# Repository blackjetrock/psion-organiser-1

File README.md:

# psion-organiser-1
Psion Organiser 1

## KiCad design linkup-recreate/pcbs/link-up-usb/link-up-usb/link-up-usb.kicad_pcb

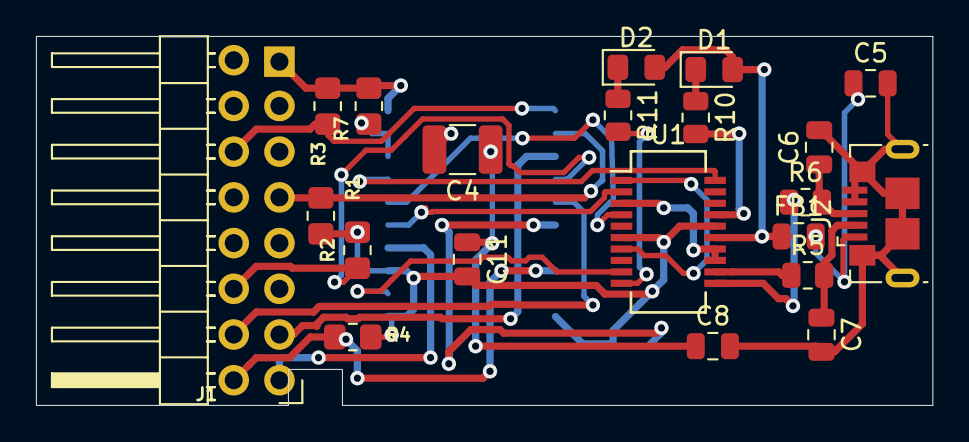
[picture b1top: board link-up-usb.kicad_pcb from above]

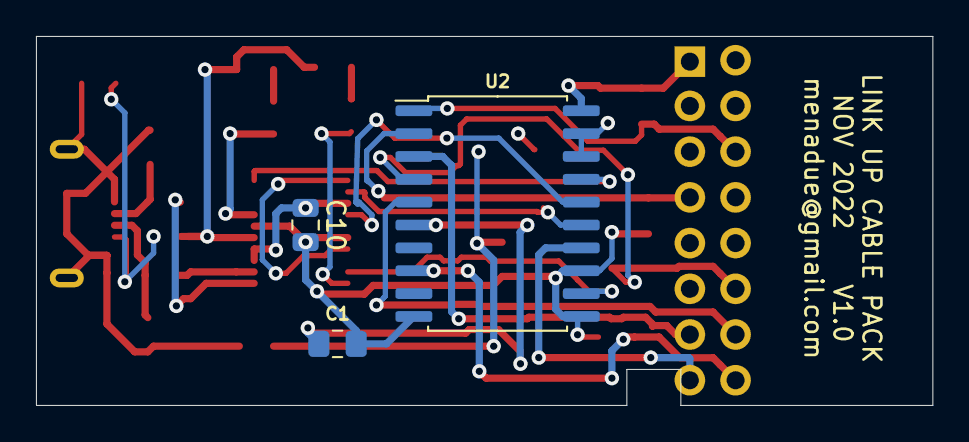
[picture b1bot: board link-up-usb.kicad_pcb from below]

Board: 4 copper layers, 49.8 x 20.5 mm, 24 parts (3 on the bottom side), 27 nets.

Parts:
C1: 100nF?; C_0805_2012Metric_Pad1.18x1.45mm_HandSolder
C4: 4u7; C_1210_3225Metric_Pad1.33x2.70mm_HandSolder
C5: 10nF; C_0805_2012Metric
C6, C7: 47pF; C_0805_2012Metric
C8, C10, C11: 100nF; C_0805_2012Metric
D1, D2: SMD LED; LED_0805_2012Metric_Pad1.15x1.40mm_HandSolder
FB1: Laird Technologies Part # MI0805K400R-10; C_0805_2012Metric
J1: Conn_02x08_Odd_Even; Psion_datapak_2x08_P2.54mm_Horizontal
J2: Connector_USB_B_Micro; USB_Micro-B_GCT_USB3076-30-A
R1, R2, R3, R4, R7: 47k; R_0805_2012Metric_Pad1.20x1.40mm_HandSolder
R5, R6: 27R; R_0805_2012Metric
R10, R11: 470R; R_0805_2012Metric
U1: FT231XS; SSOP-20_3.9x8.7mm_P0.635mm
U2: 40244; SOIC-20W_7.5x12.8mm_P1.27mm

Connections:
+5V: D1.2, D2.2, FB1.1, U1.15
+5V_LOGIC: C4.1, C8.1, C11.1
CTS: U1.9, U2.12
DTR_DSR: U1.1, U1.7
GND: C1.2, C4.2, C5.2, C6.2, C7.2, C8.2, C10.2, C11.2, J1.3, J2.4, J2.5, J2.6, R1.2, R2.2, R4.2, U1.6, U1.16, U2.10, U2.11, U2.13
unnamed: C5.1, FB1.2, J2.1
unnamed: C6.1, J2.3, R6.2
unnamed: C7.1, J2.2, R5.2
unnamed: C10.1, U1.3, U1.13, U1.14
unnamed: D1.1, R10.1
unnamed: D2.1, R11.1
unnamed: R5.1, U1.12
unnamed: R6.1, U1.11
unnamed: R7.2, U2.18, U2.19
unnamed: R10.2, U1.17
unnamed: R11.2, U1.10
RTS: U1.2, U2.15
RXD: U1.4, U2.16
SD0: J1.16, R4.1, U2.8
SD1: J1.15, U2.14
SD2: J1.14, U2.5
SD3: J1.13, U2.3
SD4: J1.12, R2.1, U2.4
SMR: J1.7, R1.1, U2.2
SS: J1.6, R3.2, U2.1
SVCC: C1.1, J1.1, R3.1, R7.1, U2.6, U2.20
TXD: U1.20, U2.17

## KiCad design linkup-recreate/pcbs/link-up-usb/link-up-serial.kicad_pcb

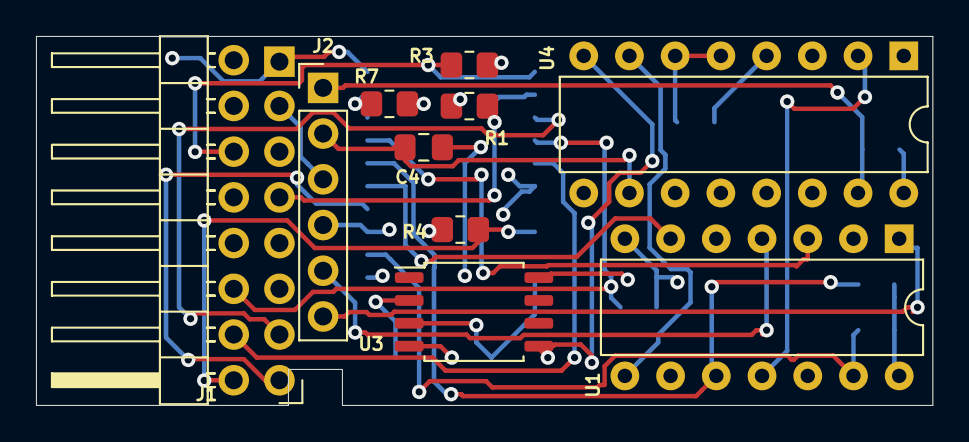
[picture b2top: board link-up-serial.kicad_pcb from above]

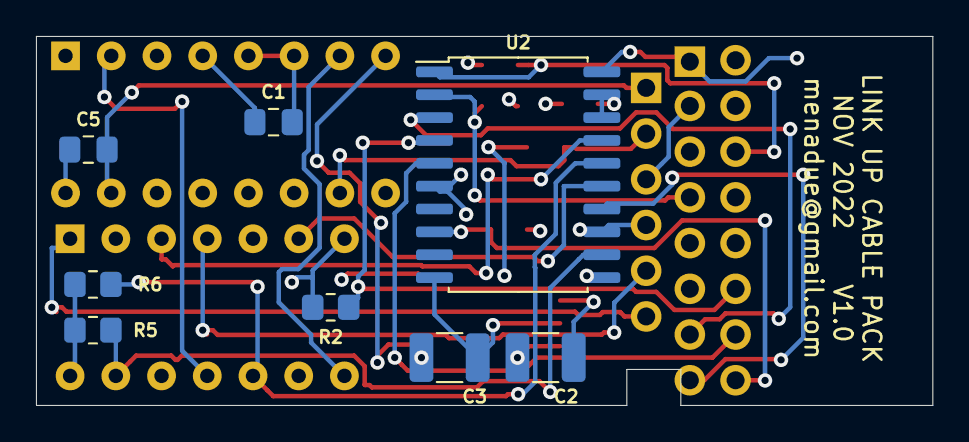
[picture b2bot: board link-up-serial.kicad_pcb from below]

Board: 4 copper layers, 49.8 x 20.5 mm, 18 parts (8 on the bottom side), 25 nets.

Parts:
C1: 100nF?; C_0805_2012Metric_Pad1.18x1.45mm_HandSolder
C2, C3: 10uF 16V; C_1210_3225Metric_Pad1.33x2.70mm_HandSolder
C4, C5: 20pF - 10nF; C_0805_2012Metric_Pad1.18x1.45mm_HandSolder
J1: Conn_02x08_Odd_Even; Psion_datapak_2x08_P2.54mm_Horizontal
J2: Conn_01x06_Female; PinHeader_1x06_P2.54mm_Vertical
R1, R2, R3, R4, R7: 47k; R_0805_2012Metric_Pad1.20x1.40mm_HandSolder
R5, R6: 10k; R_0805_2012Metric_Pad1.20x1.40mm_HandSolder
U1: 1489; DIP-14_W7.62mm
U2: 40244; SOIC-20W_7.5x12.8mm_P1.27mm
U3: ICL7660; SOP-8_5.28x5.23mm_P1.27mm
U4: DS3691; DIP-16_W7.62mm

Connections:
-5V: C3.1, U3.5, U4.8
BLUE: J2.6, U1.1
BROWN: C5.2, J2.1, U4.15
CTS_X: U1.11, U4.2
CTS_Y: R5.2, U1.13, U2.12
GREEN: J2.5, U1.4
unnamed: C2.1, U3.2
unnamed: C2.2, U3.4
unnamed: C4.2, U4.9
unnamed: C5.1, U4.16
unnamed: R7.2, U2.18, U2.19
ORANGE: C1.2, C3.2, J1.3, J2.3, J2.4, R1.2, R2.2, R4.2, U1.7, U2.10, U2.11, U2.13, U3.3, U4.3, U4.5, U4.6
RED: C4.1, J2.2, U4.10
RTS_X: U1.6, U2.15
RXD_X: U1.8, U4.7
RXD_Y: R6.2, U1.10, U2.16
SD0: J1.16, R4.1, U2.8
SD1: J1.15, U2.14
SD2: J1.14, U2.5
SD3: J1.13, U2.3
SD4: J1.12, R2.1, U2.4
SMR: J1.7, R1.1, U2.2
SS: J1.6, R3.2, U2.1
SVCC: C1.1, J1.1, R3.1, R5.1, R6.1, R7.1, U1.14, U2.6, U2.20, U3.8, U4.1, U4.4
TXD_X: U1.3, U2.17

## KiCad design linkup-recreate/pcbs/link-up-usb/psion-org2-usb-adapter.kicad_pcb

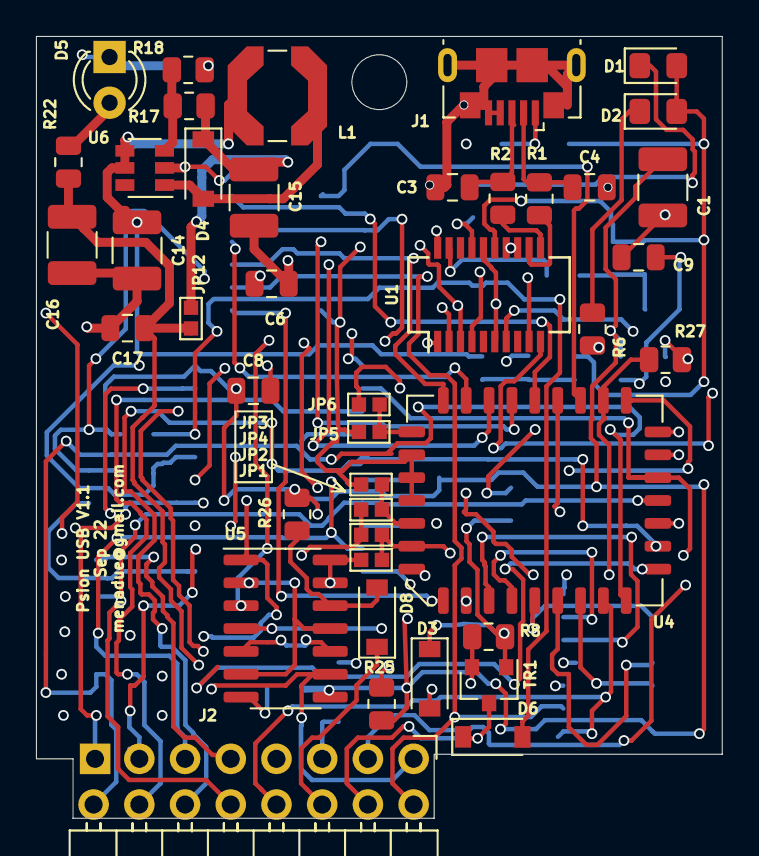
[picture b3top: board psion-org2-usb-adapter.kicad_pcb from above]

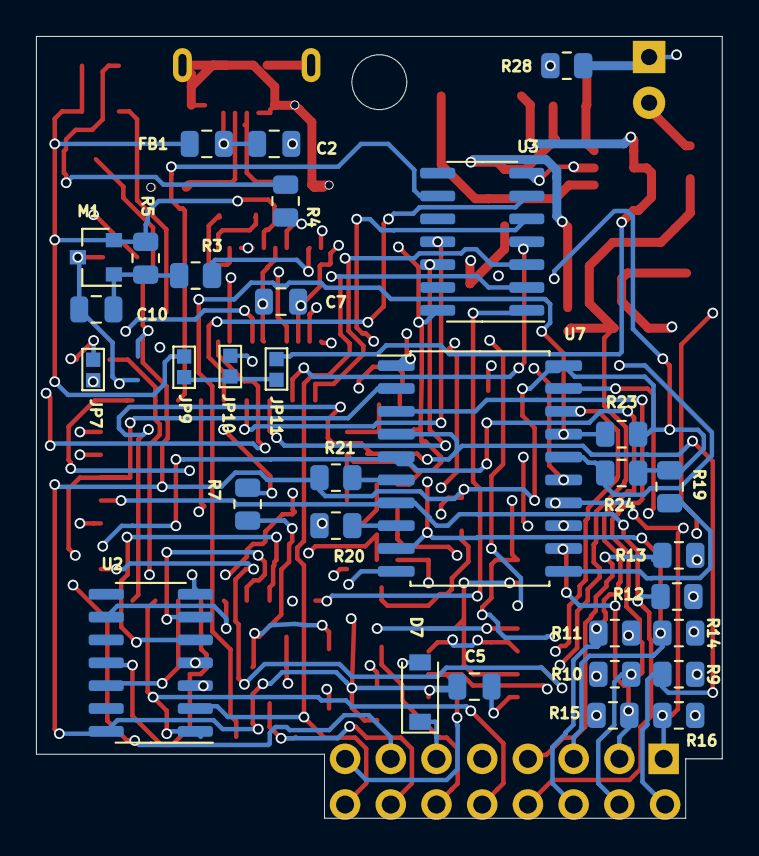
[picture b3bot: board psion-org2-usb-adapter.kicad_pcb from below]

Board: 4 copper layers, 38.1 x 43.4 mm, 74 parts (32 on the bottom side), 71 nets.

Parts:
C1: 4u7; C_1210_3225Metric_Pad1.33x2.70mm_HandSolder
C2: 10nF; C_0805_2012Metric
C3, C4: 47pF; C_0805_2012Metric
C5, C6, C7, C8, C9, C10, C17: 100nF; C_0805_2012Metric
C14, C15: 22uF; C_1210_3225Metric_Pad1.33x2.70mm_HandSolder
C16: 10uF; C_1210_3225Metric_Pad1.33x2.70mm_HandSolder
D1, D2: SMD LED; LED_0805_2012Metric_Pad1.15x1.40mm_HandSolder
D3: nopop; D_SOD-123
D4, D7: SS36; D_SOD-123
D5: LED; LED_D3.0mm
D6: D_Schottky; D_SOD-123
D8: SS36/Schottky; D_SOD-123
FB1: Laird Technologies Part # MI0805K400R-10; C_0805_2012Metric
J1: Connector_USB_B_Micro; USB_Micro-B_GCT_USB3076-30-A
J2: Conn_02x08_Odd_Even; Psion_datapak_2x08_P2.54mm_Horizontal
JP1, JP2, JP3, JP4, JP5, JP6, JP11: Jumper_NO_Small; SolderJumper-2_P1.3mm_Open_Pad0.8x0.8mm
JP7: 5V_to_logic; SolderJumper-2_P1.3mm_Open_Pad0.8x0.8mm
JP9: 5V_to_Psion; SolderJumper-2_P1.3mm_Open_Pad0.8x0.8mm
JP10: 5V_switched_to_Psion; SolderJumper-2_P1.3mm_Open_Pad0.8x0.8mm
JP12: SolderJumper_2_Open; SolderJumper-2_P1.3mm_Open_Pad0.8x0.8mm
L1: 22uH; L_Coilcraft_LPS5030
M1: P-CHANNEL-MOSFET; SOT-23
R1, R2: 27R; R_0805_2012Metric
R3, R8, R28: 1k; R_0805_2012Metric
R4, R6: 470R; R_0805_2012Metric
R5: 10k; R_0805_2012Metric
R7, R19, R20, R21, R24, R25, R26: 4k7; R_0805_2012Metric
R9, R10, R11, R12, R13, R14, R15, R16, R23, R27: 47k; R_0805_2012Metric
R17: 100k; R_0805_2012Metric
R18: 5k; R_0805_2012Metric
R22: 1k8; R_0805_2012Metric
TR1: Si2302CDS-n-channel; SOT-23
U1: FT231XS; SSOP-20_3.9x8.7mm_P0.635mm
U2, U3: 4024; SOIC-14_3.9x8.7mm_P1.27mm
U4: SST39SF020; PLCC-32_11.4x14.0mm_P1.27mm
U5: 4011; SOIC-14_3.9x8.7mm_P1.27mm
U6: Regulator_Switching_MT3608; SOT-23-6
U7: 74HC244; SOIC-20W_7.5x12.8mm_P1.27mm

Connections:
244_OE: U5.3, U7.1, U7.19
+5V: D1.2, D2.2, FB1.1, JP9.1, M1.2, R5.1, U1.15
+5V_LOGIC: C1.1, C5.1, C6.1, C8.1, JP1.2, JP3.2, JP5.2, JP7.2, R19.1, R20.1, R21.1, R23.1, R24.1, R25.1, R26.1, R27.1, U2.14, U3.14, U4.1, U4.31, U4.32, U5.8, U5.13, U5.14, U7.20
+5V_PSION: JP9.2, JP10.2, JP11.1
+5V_SWITCHED: C9.1, C10.2, JP10.1, M1.3
+10V_PSION: C16.1, C17.1, D7.2, JP12.2, R22.1
A15: JP1.1, JP2.1, U4.3
A16: JP3.1, JP4.1, U4.2
A17: JP5.1, JP6.1, U4.30
AC: D6.1, J2.14, TR1.3
CTS: R24.2, U1.9, U7.16
DTR_DSR: R7.2, U1.1, U1.7
GND: C1.2, C2.2, C3.2, C4.2, C5.2, C6.2, C7.2, C8.2, C9.2, C14.2, C15.2, C16.2, C17.2, D3.2, D5.1, J1.4, J1.5, J1.6, J2.9, JP2.2, JP4.2, JP6.2, R8.1, R9.2, R10.2, R11.2, R12.2, R13.2, R14.2, R15.2, R16.2, R28.2, TR1.2, U1.6, U1.16, U2.7, U3.7, U4.16, U5.7, U6.2, U7.10
unnamed: C2.1, FB1.2, J1.1
unnamed: C3.1, J1.3, R2.2
unnamed: C4.1, J1.2, R1.2
unnamed: C7.1, U1.3, U1.13, U1.14
unnamed: C10.1, M1.1, R3.2, R5.2
unnamed: C14.1, JP11.2, L1.1, U6.4, U6.5
unnamed: C15.1, D4.1, JP12.1, R17.1
unnamed: D1.1, R4.1
unnamed: D2.1, R6.1
unnamed: D3.1, R7.1, R8.2, TR1.1
unnamed: D4.2, L1.2, U6.1
unnamed: D5.2, R22.2
unnamed: D6.2, R23.2, U7.17
unnamed: D8.2, R26.2, U5.12
unnamed: R1.1, U1.12
unnamed: R2.1, U1.11
unnamed: R3.1, U1.19
unnamed: R4.2, U1.17
unnamed: R6.2, U1.10
unnamed: R17.2, R18.1, U6.3
unnamed: R18.2, R28.1
unnamed: R19.2, U7.11
unnamed: R20.2, U7.8
unnamed: R21.2, U7.6
unnamed: U2.3, U3.1, U4.5
unnamed: U2.4, U4.6
unnamed: U2.5, U4.7
unnamed: U2.6, U4.8
unnamed: U2.9, U4.9
unnamed: U2.11, U4.10
unnamed: U2.12, U4.11
unnamed: U3.3, U4.29
unnamed: U3.4, U4.28
unnamed: U3.5, U4.4
unnamed: U3.6, U4.25
unnamed: U3.9, U4.23
unnamed: U3.11, U4.26
unnamed: U3.12, U4.27
unnamed: U5.5, U5.10
unnamed: U5.2, U5.6, U5.11
ROMCE: R27.2, U4.22, U5.4
RTS: U1.2, U7.15
RXD: R25.2, U1.4, U7.18
SCLK: J2.10, U2.1, U4.12
SD0: J2.2, R9.1, U4.13, U7.4
SD1: J2.4, R10.1, U4.14, U7.3
SD2: J2.6, R11.1, U4.15, U7.5
SD3: J2.8, R12.1, U4.17, U7.7
SD4: J2.7, R13.1, U4.18, U7.2
SD5: J2.5, R14.1, U4.19, U7.9
SD6: J2.3, R15.1, U4.20, U7.12
SD7: J2.1, R16.1, U4.21, U7.14
SMR: J2.16, U2.2, U3.2
SOE: J2.15, U4.24, U5.1, U5.9
SS: D8.1, J2.12
SVCC: J2.13, JP7.1
TXD: U1.20, U7.13
VB: D7.1, J2.11
